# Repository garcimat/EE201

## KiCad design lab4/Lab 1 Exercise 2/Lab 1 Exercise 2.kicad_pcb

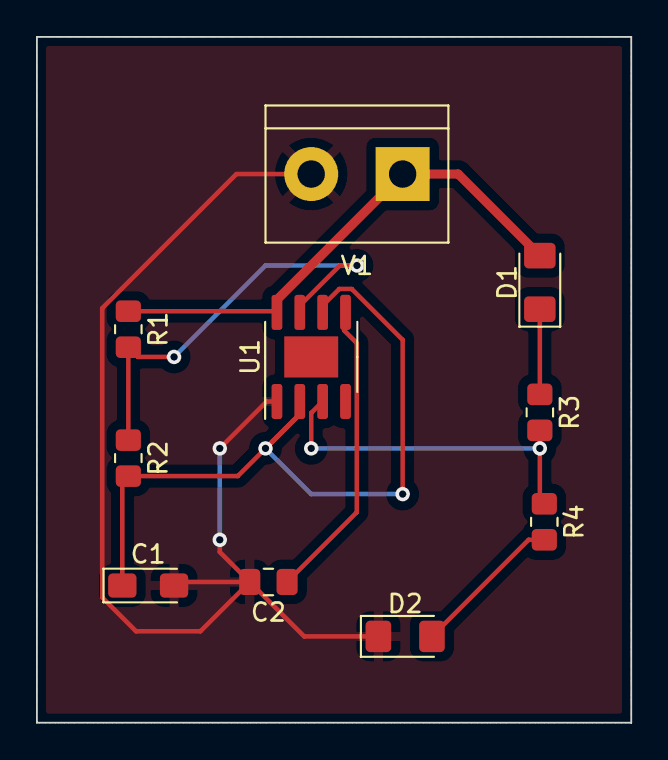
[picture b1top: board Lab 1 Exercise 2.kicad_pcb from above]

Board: 2 copper layers, 33.0 x 38.1 mm, 10 parts (0 on the bottom side), 8 nets.

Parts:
C1: 10uF; CP_EIA-3216-18_Kemet-A_Pad1.58x1.35mm_HandSolder
C2: 0.01uF; C_0805_2012Metric_Pad1.18x1.45mm_HandSolder
D1, D2: LED; LED_1206_3216Metric_Pad1.42x1.75mm_HandSolder
R1, R3, R4: 1k; R_0805_2012Metric_Pad1.20x1.40mm_HandSolder
R2: 10k; R_0805_2012Metric_Pad1.20x1.40mm_HandSolder
U1: NE555D; SOIC-8-1EP_3.9x4.9mm_P1.27mm_EP2.29x3mm
V1: 9V; TerminalBlock_bornier-2_P5.08mm

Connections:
/pin_2: C1.1, R2.2, U1.2 (TR), U1.6 (THR)
/pin_3: R3.2, R4.1, U1.3 (Q)
/pin_7: R1.2, R2.1, U1.7 (DIS)
GND: C1.2, C2.2, D2.1 (K), U1.1 (GND), V1.2
unnamed: C2.1, U1.5 (CV)
unnamed: D1.1 (K), R3.1
unnamed: D1.2 (A), R1.1, U1.8 (VCC), V1.1
unnamed: D2.2 (A), R4.2

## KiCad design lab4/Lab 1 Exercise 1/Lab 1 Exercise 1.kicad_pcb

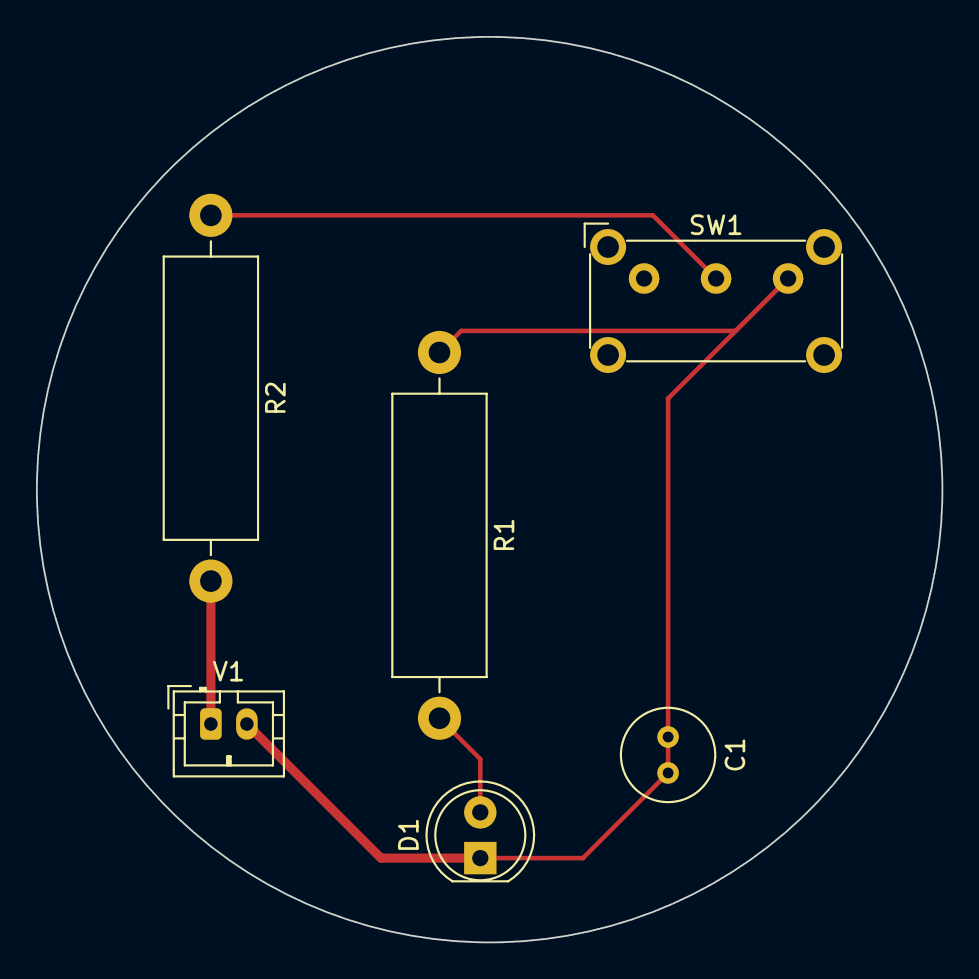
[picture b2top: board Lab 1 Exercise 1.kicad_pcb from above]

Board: 2 copper layers, 50.3 x 50.3 mm, 6 parts (0 on the bottom side), 4 nets.

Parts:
C1: 4.7u Ferads; C_Radial_D5.0mm_H5.0mm_P2.00mm
D1: LED; LED_D5.0mm
R1: 20k Ohms; R_Axial_DIN0516_L15.5mm_D5.0mm_P20.32mm_Horizontal
R2: 2.2k Ohms; R_Axial_DIN0516_L15.5mm_D5.0mm_P20.32mm_Horizontal
SW1: SW_SPDT; SW_E-Switch_EG1224_SPDT_Angled
V1: 9 V; JST_PH_B2B-PH-K_1x02_P2.00mm_Vertical

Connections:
unnamed: C1.1, C1.2, D1.1 (K), R1.1, SW1.3 (C), V1.2
unnamed: D1.2 (A), R1.2
unnamed: R2.1, SW1.2 (B)
unnamed: R2.2, V1.1

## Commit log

2023-01-13 This is a test comments
2023-01-13 Test Comment
2023-01-13 This is a test comment
2023-01-13 Commiting aboutMe
2023-01-13 added A
2023-01-20 Committing Arduino
2023-01-27 Commiting lab4
2023-02-03 Commiting Soldering
2023-02-17 Commiting Lab5
2023-03-10 Commiting FinalProject
